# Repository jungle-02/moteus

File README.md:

# moteus brushless servo #

This contains full designs for the moteus brushless servo actuator,
including firmware and PCBs.

**WARNING**: This is not just a software project.  It includes designs
for moderately high power electronics.  It has not yet burned down my
(or anyone's that I know of) house, but there are no guarantees.

# Specifications #

| Name                   | r4.11        | c1         | n1        | x1          |
|------------------------|--------------|------------|-----------|-------------|
| Voltage Input          | 10-44V       | 10-51V     | 10-54V    | 10-54V      |
| Peak Electrical Power  | 900W @ 30V   | 250W @ 28V | 2kW @ 36V | 1.3kW @ 36V |
| Mass                   | 14.2g        | 8.9g       | 14.6g     | 23.8g       |
| Control Rate           | 15-30kHz     | -          | -         | -           |
| PWM Switching Rate     | 15-60kHz     | -          | -         | -           |
| CPU                    | STM32G4      | -          | -         | -           |
| Uncooled phase current | 12A          | 5A         | 9A       | 25A         |
| Cooled phase current   | 32A          | 14A        | 26A       | 62A         |
| Peak phase current     | 100A         | 20A        | 100A      | 120A        |
| Communications         | 5Mbps CAN-FD | -          | -         | -           |
| Dimensions             | 46x53mm      | 38x38x9mm  | 46x46x8mm | 56x56x10mm  |

Assembled and tested boards can be purchased at: https://mjbots.com

# Directory structure #

* hw/ - hardware (mechanical and electrical designs)
  * controller/ - PCB design for moteus-r4.11
  * c1/ - PCB design for moteus-c1
  * n1/ - PCB design for moteus-n1
  * x1/ - PCB design for moteus-x1
* fw/ - firmware for brushless controller
* lib/ - client side software
* utils/ - diagnostic tools
* tools/ - bazel build configure
* docs/ - documentation

# Documentation #

* [Quick Start](https://mjbots.github.io/moteus/quick-start)
* [All Documentation](https://mjbots.github.io/moteus/)
* [Discord](https://discord.gg/W4hUpBb)

# Misc #

 * 

# How to support moteus development #

The easiest way to support development the moteus hardware and firmware is as follows:

1) Buy things from https://mjbots.com
2) Build awesome machines!

That's it!  If for some reason you want to go above and beyond, you can sponsor mjbots through github: https://github.com/sponsors/mjbots

# License #

All files contained in this repository, unless otherwise noted, are
available under an Apache 2.0 License:
https://www.apache.org/licenses/LICENSE-2.0

# Trademark #

mjbots Robotic Systems LLC owns and protects the "mjbots" and "moteus" trademarks in many jurisdictions.

If you want to use these names in your project or product, please read the [Trademark Policy](https://mjbots.com/trademark-policy)

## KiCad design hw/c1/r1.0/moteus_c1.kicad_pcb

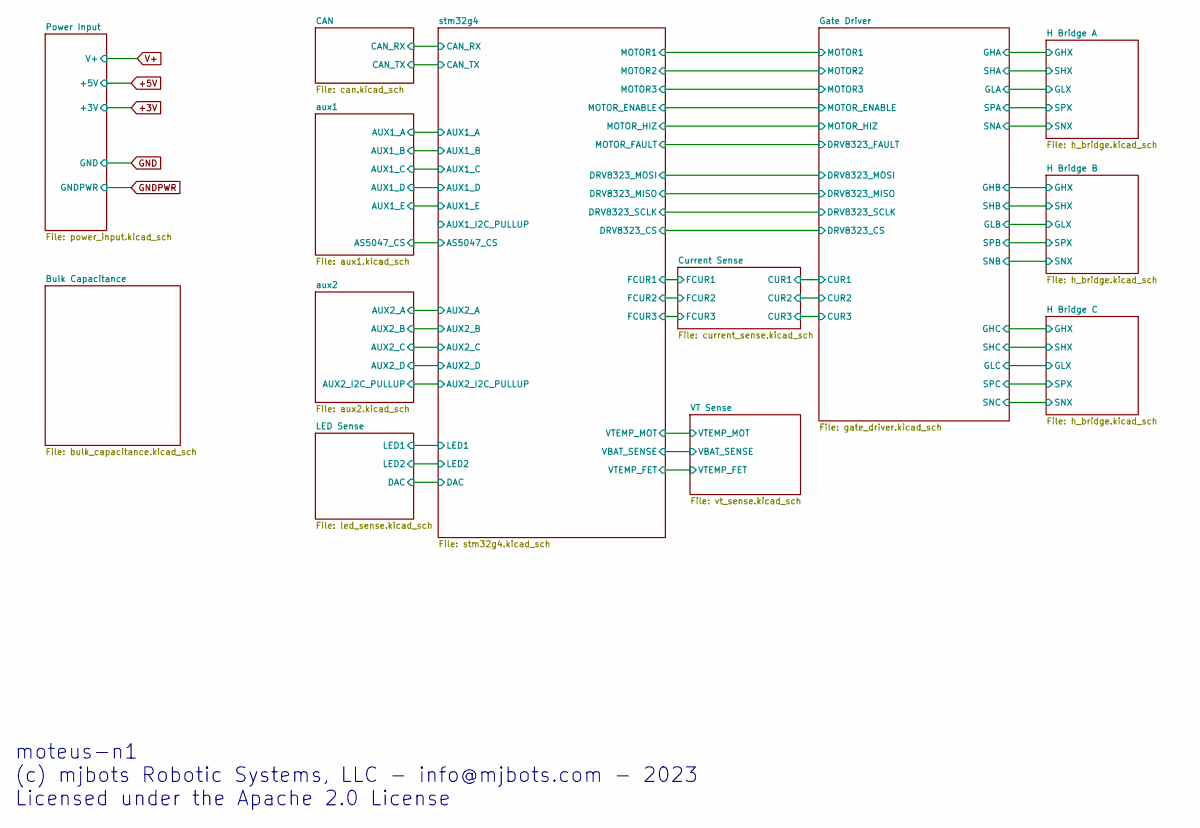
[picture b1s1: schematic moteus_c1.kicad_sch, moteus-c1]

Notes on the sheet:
moteus-n1 (c) mjbots Robotic Systems, LLC - info@mjbots.com - 2023 Licensed under the Apache 2.0 License

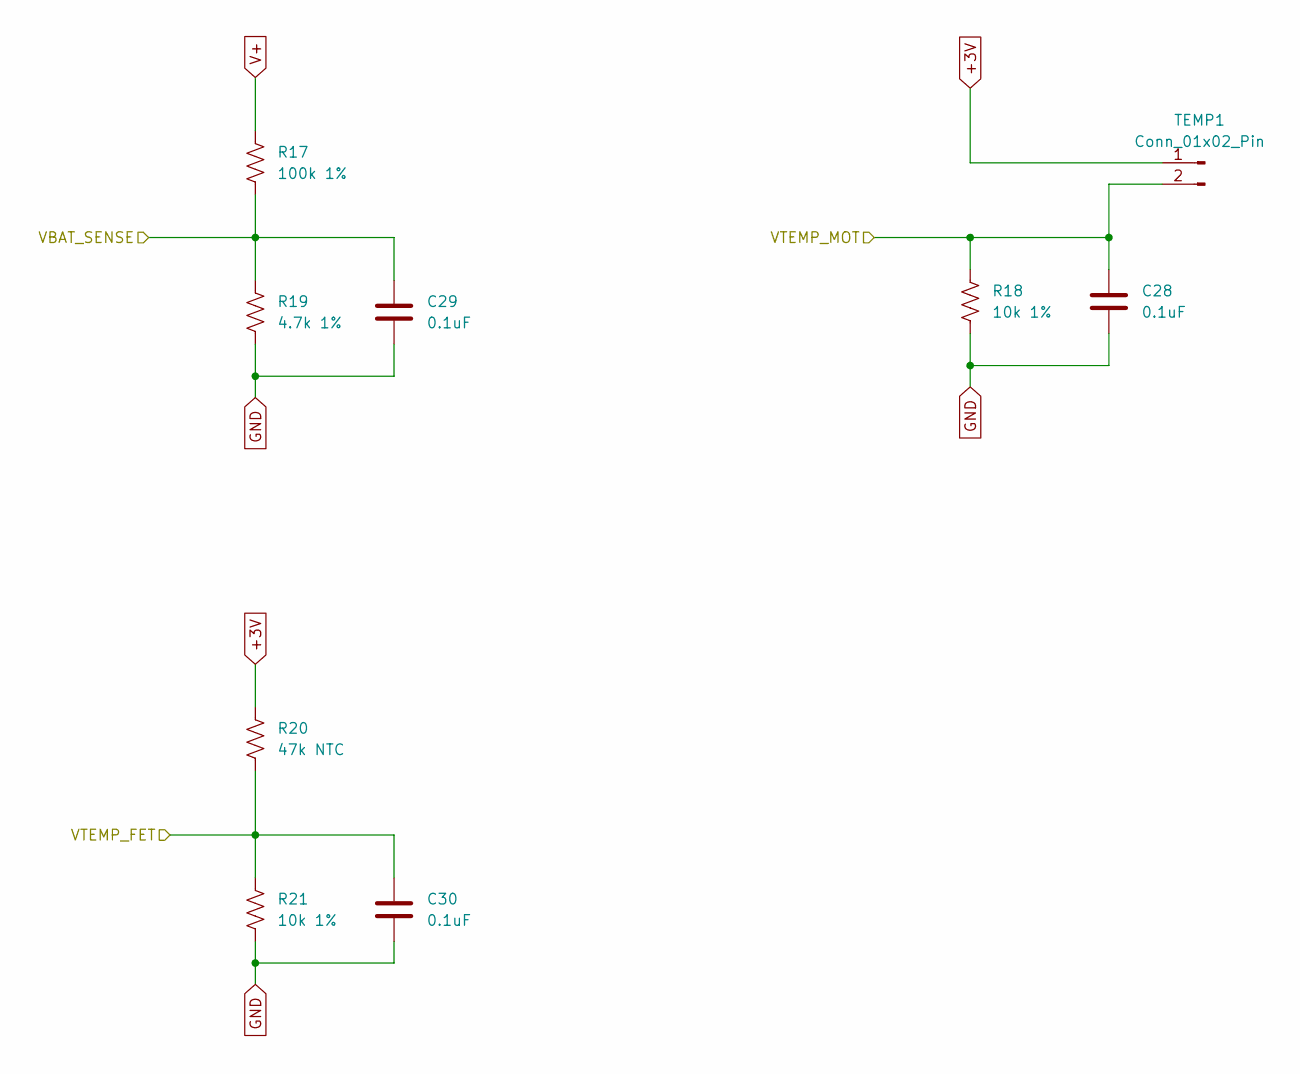
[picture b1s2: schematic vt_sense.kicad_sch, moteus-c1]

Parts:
C28, C29, C30: 0.1uF; C_0402_1005Metric; MPN MF-CAP-0402-0.1uF
R17: 100k 1%; R_0402_1005Metric; MPN RC0402FR-07100KL
R18, R21: 10k 1%; R_0402_1005Metric; MPN RC0402FR-0710KL
R19: 4.7k 1%; R_0402_1005Metric; MPN RC0402FR-074K7L
R20: 47k NTC; R_0402_1005Metric; MPN NCP15WB473F03RC
TEMP1: Conn_01x02_Pin; PinHeader_1x02_P2.00mm_Vertical

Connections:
/VT Sense/VBAT_SENSE: C29.1, R17.2, R19.1; also elsewhere on the board
/VT Sense/VTEMP_FET: C30.1, R20.2, R21.1; also elsewhere on the board
/VT Sense/VTEMP_MOT: C28.1, R18.1, TEMP1.2; also elsewhere on the board
V+: R17.1; also elsewhere on the board

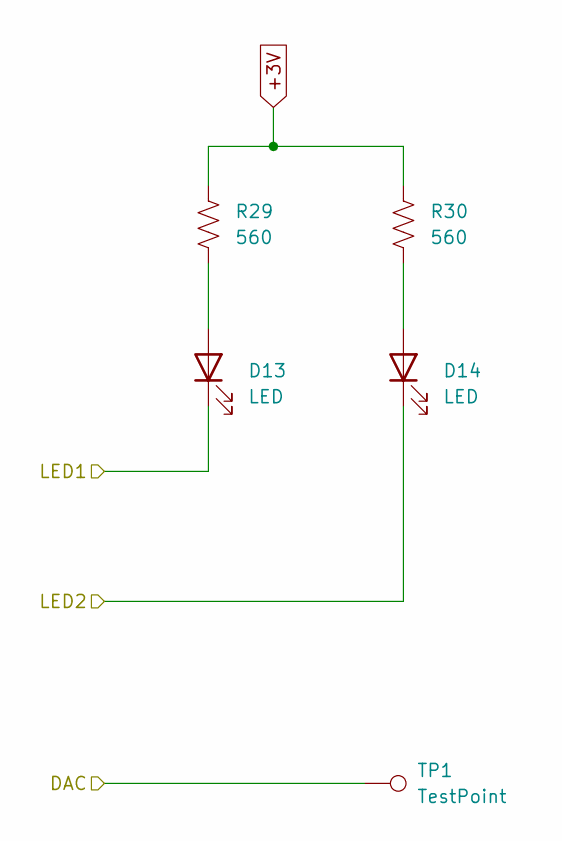
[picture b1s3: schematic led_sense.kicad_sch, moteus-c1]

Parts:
D13: LED; LED_0603_1608Metric; MPN MF-LED-0603-RED
D14: LED; LED_0603_1608Metric; MPN MF-LED-0603-GREEN
R29, R30: 560; R_0402_1005Metric; MPN MF-RES-0402-560
TP1: TestPoint; TestPoint_THTPad_D1.0mm_Drill0.5mm

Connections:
/LED Sense/LED1: D13.1 (K); also elsewhere on the board
/LED Sense/LED2: D14.1 (K); also elsewhere on the board
unnamed: D13.2 (A), R29.2
unnamed: D14.2 (A), R30.2

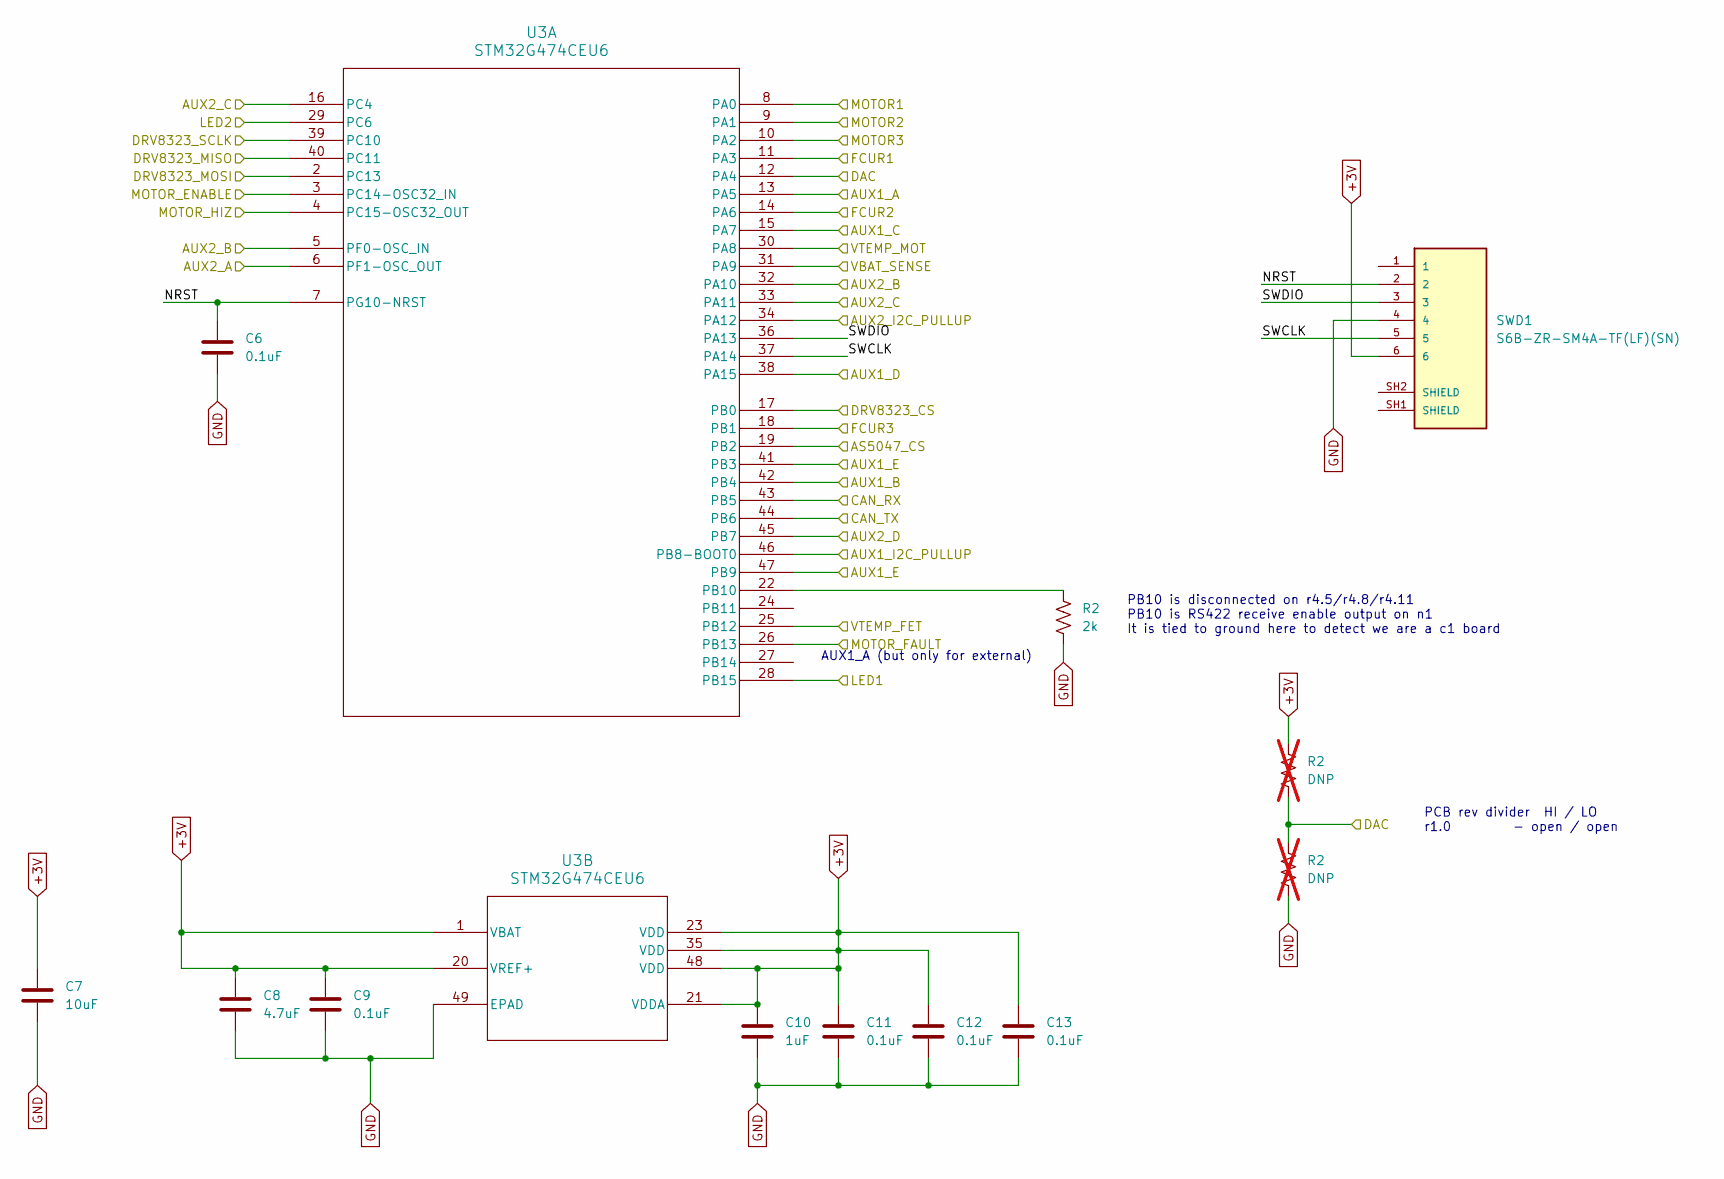
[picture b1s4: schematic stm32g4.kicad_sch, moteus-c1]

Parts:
C6, C9, C11, C12, C13: 0.1uF; C_0402_1005Metric; MPN MF-CAP-0402-0.1uF
C7: 10uF; C_1206_3216Metric; MPN MF-CAP-1206-10uF
C8: 4.7uF; C_0603_1608Metric; MPN CL10A475KP8NNNC
C10: 1uF; C_0402_1005Metric; MPN MF-CAP-0402-1uF
R2: 2k; R_0402_1005Metric; MPN MF-RES-0402-2K
SWD1: S6B-ZR-SM4A-TF(LF)(SN); JST_S6B-ZR-SM4A-TF(LF)(SN); MPN S6B-ZR-SM4A-TF(LF)(SN)
U3: STM32G474CEU6; UFQFPN-48_7X7X0P55MM; MPN STM32G474CEU6

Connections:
/CAN/CAN_RX: U3.43 (PB5); also elsewhere on the board
/CAN/CAN_TX: U3.44 (PB6); also elsewhere on the board
/Current Sense/FCUR1: U3.11 (PA3); also elsewhere on the board
/Current Sense/FCUR2: U3.14 (PA6); also elsewhere on the board
/Current Sense/FCUR3: U3.18 (PB1); also elsewhere on the board
/Gate Driver/DRV8323_CS: U3.17 (PB0); also elsewhere on the board
/Gate Driver/DRV8323_FAULT: U3.26 (PB13); also elsewhere on the board
/Gate Driver/DRV8323_MOSI: U3.2 (PC13); also elsewhere on the board
/Gate Driver/DRV8323_SCLK: U3.39 (PC10); also elsewhere on the board
/Gate Driver/MOTOR1: U3.8 (PA0); also elsewhere on the board
/Gate Driver/MOTOR2: U3.9 (PA1); also elsewhere on the board
/Gate Driver/MOTOR3: U3.10 (PA2); also elsewhere on the board
/Gate Driver/MOTOR_ENABLE: U3.3 (PC14-OSC32_IN); also elsewhere on the board
/Gate Driver/MOTOR_HIZ: U3.4 (PC15-OSC32_OUT); also elsewhere on the board
/LED Sense/LED1: U3.28 (PB15); also elsewhere on the board
/LED Sense/LED2: U3.29 (PC6); also elsewhere on the board
/VT Sense/VBAT_SENSE: U3.31 (PA9); also elsewhere on the board
/VT Sense/VTEMP_FET: U3.25 (PB12); also elsewhere on the board
/VT Sense/VTEMP_MOT: U3.30 (PA8); also elsewhere on the board
/aux1/AS5047_CS: U3.19 (PB2); also elsewhere on the board
/aux1/AUX1_A: U3.13 (PA5); also elsewhere on the board
/aux1/AUX1_B: U3.42 (PB4); also elsewhere on the board
/aux1/AUX1_C: U3.15 (PA7); also elsewhere on the board
/aux1/AUX1_D: U3.38 (PA15); also elsewhere on the board
/aux1/AUX1_E: U3.41 (PB3), U3.47 (PB9); also elsewhere on the board
/aux2/AUX2_A: U3.6 (PF1-OSC_OUT); also elsewhere on the board
/aux2/AUX2_B: U3.5 (PF0-OSC_IN), U3.32 (PA10); also elsewhere on the board
/aux2/AUX2_C: U3.16 (PC4), U3.33 (PA11); also elsewhere on the board
/aux2/AUX2_D: U3.45 (PB7); also elsewhere on the board
/aux2/AUX2_I2C_PULLUP: U3.34 (PA12); also elsewhere on the board
/stm32g4/AUX1_I2C_PULLUP: U3.46 (PB8-BOOT0)
/stm32g4/NRST: C6.1, SWD1.2, U3.7 (PG10-NRST)
/stm32g4/SWCLK: SWD1.5, U3.37 (PA14)
/stm32g4/SWDIO: SWD1.3, U3.36 (PA13)

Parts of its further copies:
R31: 2k; R_0402_1005Metric; MPN MF-RES-0402-2K

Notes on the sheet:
PB10 is disconnected on r4.5/r4.8/r4.11 PB10 is RS422 receive enable output on n1 It is tied to ground here to detect we are a c1 board
PCB rev divider HI / LO r1.0 - open / open
AUX1_A (but only for external)

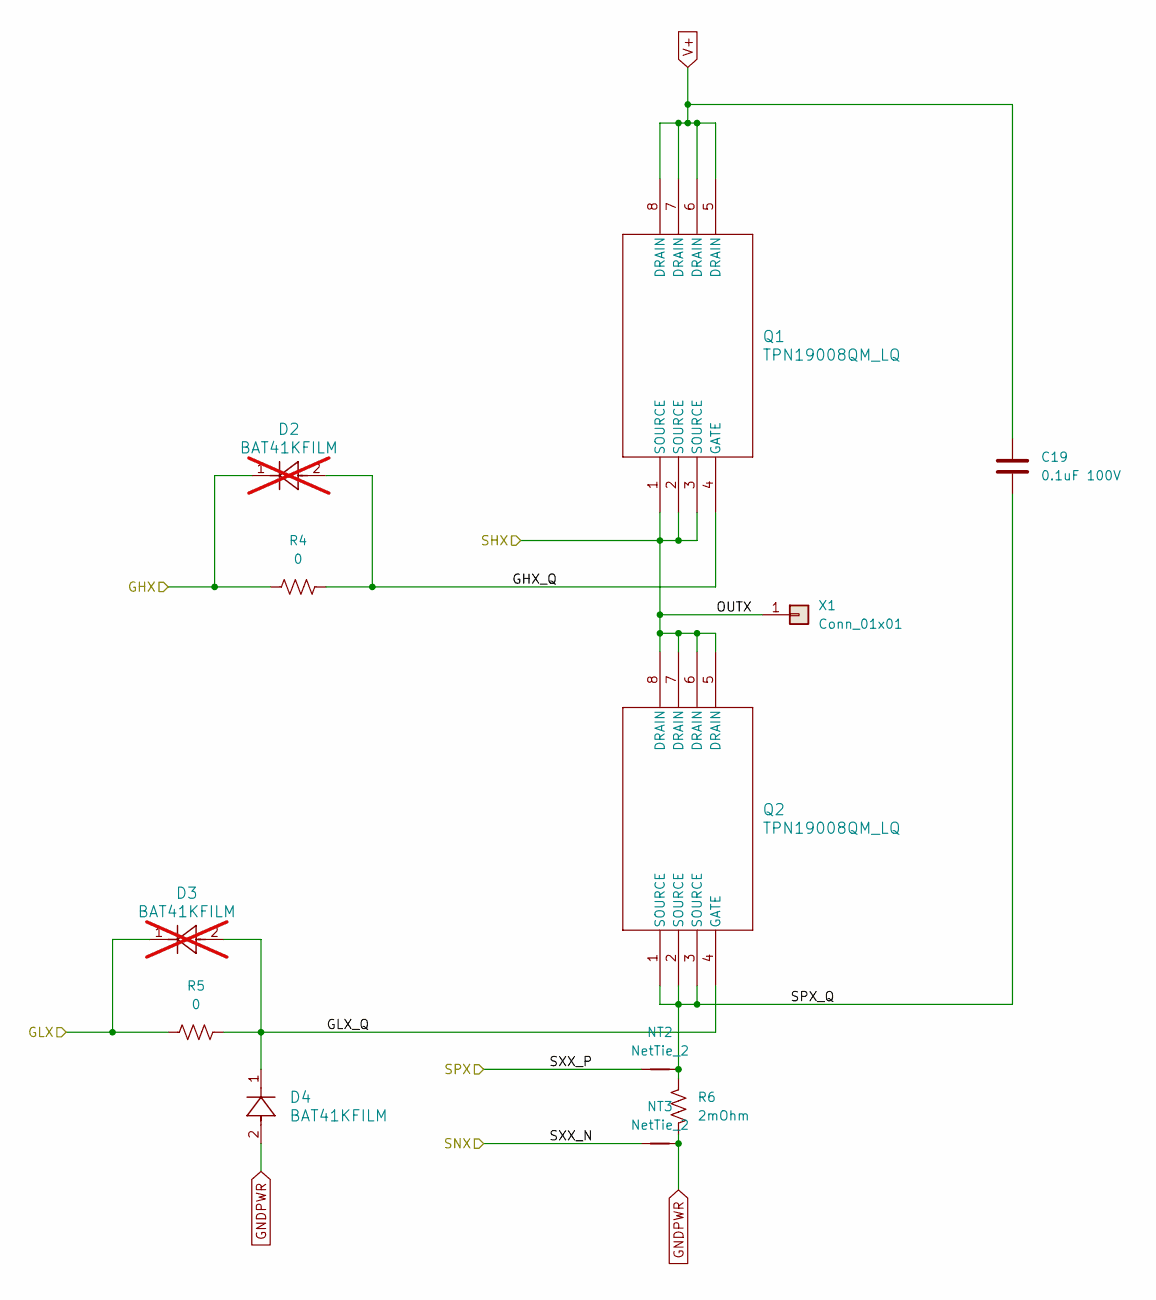
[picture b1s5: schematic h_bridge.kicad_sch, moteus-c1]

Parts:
C19: 0.1uF 100V; C_1206_3216Metric; MPN 12061C104KAT2A
D2, D3: BAT41KFILM; SOD-523_STM; MPN BAT41KFILM; not fitted
D4: BAT41KFILM; SOD-523_STM; MPN BAT41KFILM
NT2, NT3: NetTie_2; NetTie-2_SMD_Pad0.254mm
Q1, Q2: TPN19008QM_LQ; TSON Advance_TOS; MPN TPN19008QM,LQ
R4: 0; R_0402_1005Metric; MPN MF-RES-0402-0
R5: 0; R_0805_2012Metric; MPN MF-RES-0402-0
R6: 2mOhm; R_0805_2012Metric; MPN CSSH0805FT2L00
X1: Conn_01x01; POWER_M2.5

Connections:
/Gate Driver/GHA: D2.1, R4.1; also elsewhere on the board
/Gate Driver/GLA: D3.1, R5.1; also elsewhere on the board
/H Bridge A/GHX_Q: D2.2, Q1.4 (GATE), R4.2
/H Bridge A/GLX_Q: D3.2, D4.1, Q2.4 (GATE), R5.2
/H Bridge A/OUTX: Q1.1 (SOURCE), Q1.2 (SOURCE), Q1.3 (SOURCE), Q2.5 (DRAIN), Q2.6 (DRAIN), Q2.7 (DRAIN), Q2.8 (DRAIN), X1.1; also elsewhere on the board
/H Bridge A/SPX_Q: C19.2, NT2.2, Q2.1 (SOURCE), Q2.2 (SOURCE), Q2.3 (SOURCE), R6.1
/H Bridge A/SXX_N: NT3.1; also elsewhere on the board
/H Bridge A/SXX_P: NT2.1; also elsewhere on the board
GNDPWR: D4.2, NT3.2, R6.2; also elsewhere on the board
V+: C19.1, Q1.5 (DRAIN), Q1.6 (DRAIN), Q1.7 (DRAIN), Q1.8 (DRAIN); also elsewhere on the board

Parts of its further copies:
C20, C21: 0.1uF 100V; C_1206_3216Metric; MPN 12061C104KAT2A
D5, D6, D8, D9: BAT41KFILM; SOD-523_STM; MPN BAT41KFILM; not fitted
D7, D10: BAT41KFILM; SOD-523_STM; MPN BAT41KFILM
NT4, NT5, NT6, NT7: NetTie_2; NetTie-2_SMD_Pad0.254mm
Q3, Q4, Q5, Q6: TPN19008QM_LQ; TSON Advance_TOS; MPN TPN19008QM,LQ
R7, R10: 0; R_0402_1005Metric; MPN MF-RES-0402-0
R8, R11: 0; R_0805_2012Metric; MPN MF-RES-0402-0
R9, R12: 2mOhm; R_0805_2012Metric; MPN CSSH0805FT2L00
X2, X3: Conn_01x01; POWER_M2.5

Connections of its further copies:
/Gate Driver/GHB: D5.1, R7.1; also elsewhere on the board
/Gate Driver/GHC: D8.1, R10.1; also elsewhere on the board
/Gate Driver/GLB: D6.1, R8.1; also elsewhere on the board
/Gate Driver/GLC: D9.1, R11.1; also elsewhere on the board
/H Bridge B/GHX_Q: D5.2, Q3.4 (GATE), R7.2
/H Bridge B/GLX_Q: D6.2, D7.1, Q4.4 (GATE), R8.2
/H Bridge B/OUTX: Q3.1 (SOURCE), Q3.2 (SOURCE), Q3.3 (SOURCE), Q4.5 (DRAIN), Q4.6 (DRAIN), Q4.7 (DRAIN), Q4.8 (DRAIN), X2.1; also elsewhere on the board
/H Bridge B/SPX_Q: C20.2, NT4.2, Q4.1 (SOURCE), Q4.2 (SOURCE), Q4.3 (SOURCE), R9.1
/H Bridge B/SXX_N: NT5.1; also elsewhere on the board
/H Bridge B/SXX_P: NT4.1; also elsewhere on the board
/H Bridge C/GHX_Q: D8.2, Q5.4 (GATE), R10.2
/H Bridge C/GLX_Q: D9.2, D10.1, Q6.4 (GATE), R11.2
/H Bridge C/OUTX: Q5.1 (SOURCE), Q5.2 (SOURCE), Q5.3 (SOURCE), Q6.5 (DRAIN), Q6.6 (DRAIN), Q6.7 (DRAIN), Q6.8 (DRAIN), X3.1; also elsewhere on the board
/H Bridge C/SPX_Q: C21.2, NT6.2, Q6.1 (SOURCE), Q6.2 (SOURCE), Q6.3 (SOURCE), R12.1
/H Bridge C/SXX_N: NT7.1; also elsewhere on the board
/H Bridge C/SXX_P: NT6.1; also elsewhere on the board
GNDPWR: D7.2, D10.2, NT5.2, NT7.2, R9.2, R12.2; also elsewhere on the board
V+: C20.1, C21.1, Q3.5 (DRAIN), Q3.6 (DRAIN), Q3.7 (DRAIN), Q3.8 (DRAIN), Q5.5 (DRAIN), Q5.6 (DRAIN), Q5.7 (DRAIN), Q5.8 (DRAIN); also elsewhere on the board

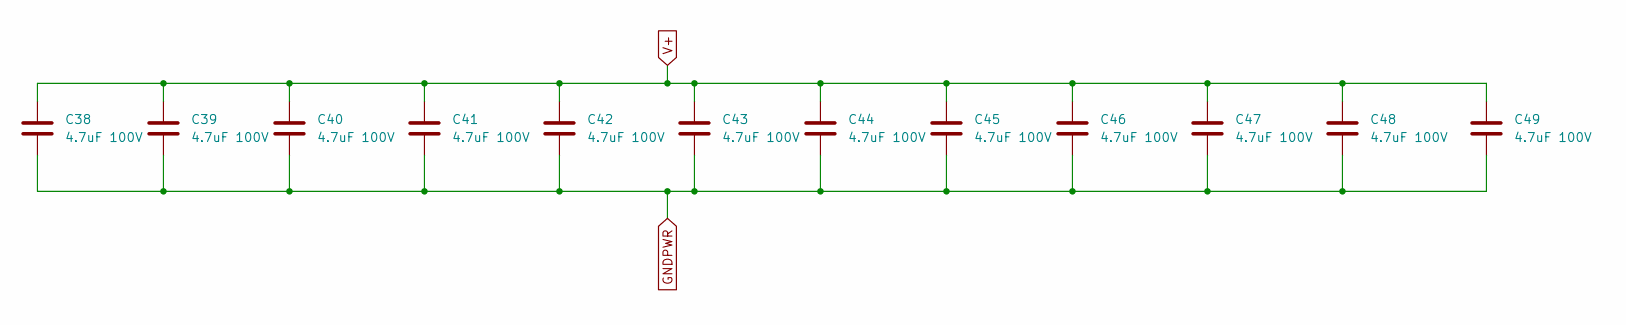
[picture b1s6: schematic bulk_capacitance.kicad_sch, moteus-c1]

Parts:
C38, C39, C40, C41, C42, C43, C44, C45, C46, C47, C48, C49: 4.7uF 100V; C_1206_3216Metric; MPN GRJ31CC72A475KE01K

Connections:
GNDPWR: C38.2, C39.2, C40.2, C41.2, C42.2, C43.2, C44.2, C45.2, C46.2, C47.2, C48.2, C49.2; also elsewhere on the board
V+: C38.1, C39.1, C40.1, C41.1, C42.1, C43.1, C44.1, C45.1, C46.1, C47.1, C48.1, C49.1; also elsewhere on the board

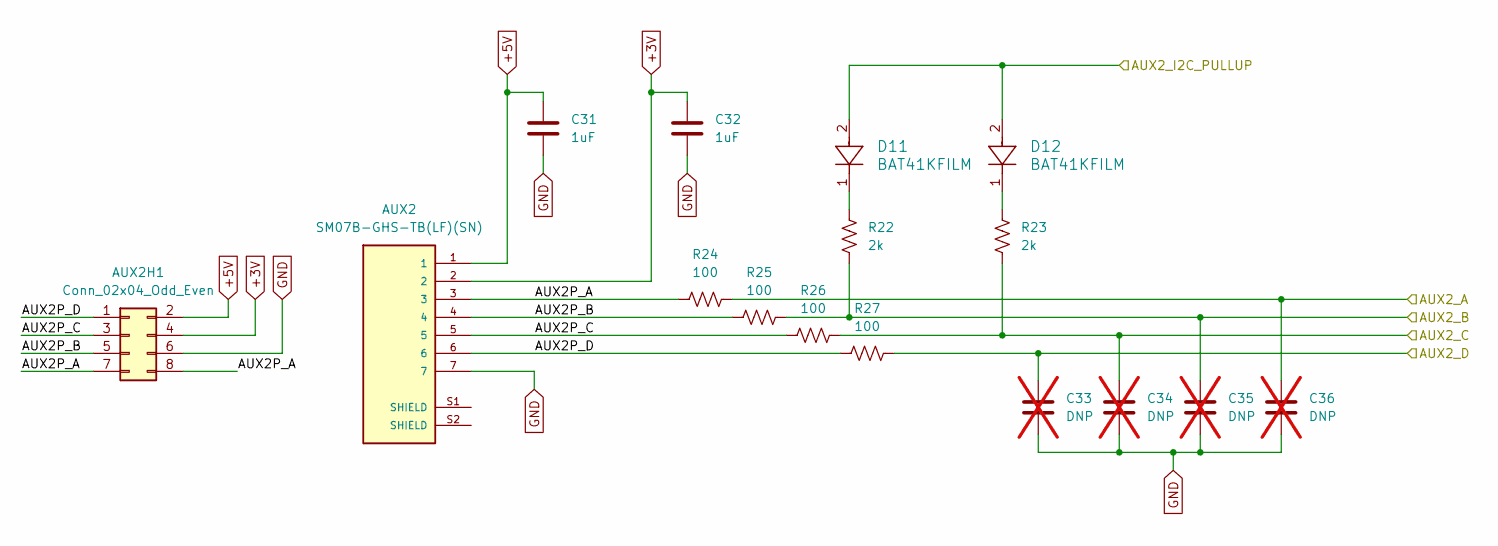
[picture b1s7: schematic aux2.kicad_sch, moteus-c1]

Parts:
AUX2: SM07B-GHS-TB(LF)(SN); JST_SM07B-GHS-TB(LF)(SN); MPN SM07B-GHS-TB(LF)(SN)
AUX2H1: Conn_02x04_Odd_Even; PinHeader_2x04_P1.27mm_Vertical
C31, C32: 1uF; C_0402_1005Metric; MPN MF-CAP-0402-1uF
C33, C34, C35, C36: DNP; C_0402_1005Metric; not fitted
D11, D12: BAT41KFILM; SOD-523_STM; MPN BAT41KFILM
R22, R23: 2k; R_0402_1005Metric; MPN MF-RES-0402-2K
R24, R25, R26, R27: 100; R_0402_1005Metric; MPN MF-RES-0402-100

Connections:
+5V: AUX2.1, AUX2H1.2, C31.1; also elsewhere on the board
/aux2/AUX2P_B: AUX2.4, AUX2H1.5, R25.1
/aux2/AUX2P_C: AUX2.5, AUX2H1.3, R26.1
/aux2/AUX2P_D: AUX2.6, AUX2H1.1, R27.1
/aux2/AUX2_A: C36.1, R24.2; also elsewhere on the board
/aux2/AUX2_B: C35.1, R22.2, R25.2; also elsewhere on the board
/aux2/AUX2_C: C34.1, R23.2, R26.2; also elsewhere on the board
/aux2/AUX2_D: C33.1, R27.2; also elsewhere on the board
/aux2/AUX2_I2C_PULLUP: D11.2, D12.2; also elsewhere on the board
unnamed: D11.1, R22.1
unnamed: D12.1, R23.1

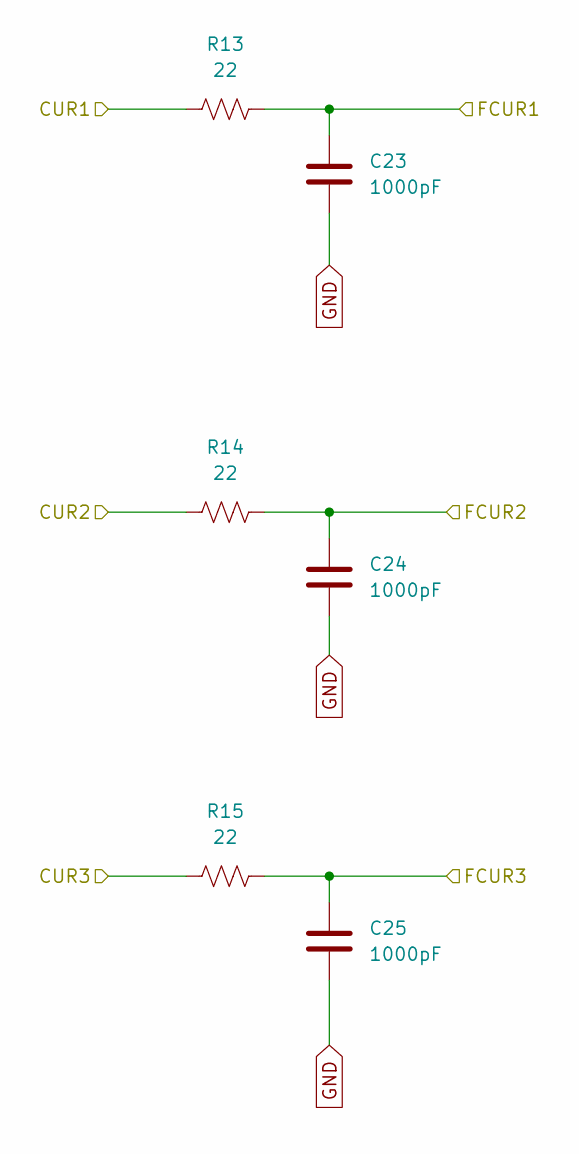
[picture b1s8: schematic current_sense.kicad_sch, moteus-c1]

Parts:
C23, C24, C25: 1000pF; C_0402_1005Metric; MPN MF-CAP-0402-1nF
R13, R14, R15: 22; R_0402_1005Metric; MPN MF-RES-0402-22

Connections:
/Current Sense/CUR1: R13.1; also elsewhere on the board
/Current Sense/CUR2: R14.1; also elsewhere on the board
/Current Sense/CUR3: R15.1; also elsewhere on the board
/Current Sense/FCUR1: C23.1, R13.2; also elsewhere on the board
/Current Sense/FCUR2: C24.1, R14.2; also elsewhere on the board
/Current Sense/FCUR3: C25.1, R15.2; also elsewhere on the board

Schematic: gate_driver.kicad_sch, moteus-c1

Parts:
C14: 1uF 25V; C_0603_1608Metric; MPN C1608X7R1E105K080AE
C15: 0.1uF 100V; C_0603_1608Metric; MPN GCJ188R72A104KA01D
C16: 47nF 100V; C_0603_1608Metric; MPN C0603X473K1RAC7867
C17: 1uF; C_0402_1005Metric; MPN MF-CAP-0402-1uF
C18: 1uF; C_0603_1608Metric; MPN MF-CAP-0603-1uF
R2, R3: 2k; R_0402_1005Metric; MPN MF-RES-0402-2K
U4: DRV8323SRTAR; RTA0040B; MPN DRV8323SRTAR

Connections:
/Current Sense/CUR1: U4.21 (SOC); also elsewhere on the board
/Current Sense/CUR2: U4.22 (SOB); also elsewhere on the board
/Current Sense/CUR3: U4.23 (SOA); also elsewhere on the board
/Gate Driver/DRV8323_CS: U4.29 (GAIN_SCS_N); also elsewhere on the board
/Gate Driver/DRV8323_FAULT: R3.2, U4.25 (FAULT_N); also elsewhere on the board
/Gate Driver/DRV8323_MOSI: U4.27 (IDRIVE_SDI); also elsewhere on the board
/Gate Driver/DRV8323_SCLK: U4.28 (VDS_SCLK); also elsewhere on the board
/Gate Driver/GHA: U4.6 (GHA); also elsewhere on the board
/Gate Driver/GHB: U4.15 (GHB); also elsewhere on the board
/Gate Driver/GHC: U4.16 (GHC); also elsewhere on the board
/Gate Driver/GLA: U4.8 (GLA); also elsewhere on the board
/Gate Driver/GLB: U4.13 (GLB); also elsewhere on the board
/Gate Driver/GLC: U4.18 (GLC); also elsewhere on the board
/Gate Driver/MOTOR1: U4.34 (INHA); also elsewhere on the board
/Gate Driver/MOTOR2: U4.36 (INHB); also elsewhere on the board
/Gate Driver/MOTOR3: U4.38 (INHC); also elsewhere on the board
/Gate Driver/MOTOR_ENABLE: U4.30 (ENABLE); also elsewhere on the board
/Gate Driver/MOTOR_HIZ: U4.35 (INLA), U4.37 (INLB), U4.39 (INLC); also elsewhere on the board
/H Bridge A/OUTX: U4.7 (SHA); also elsewhere on the board
/H Bridge A/SXX_N: U4.10 (SNA); also elsewhere on the board
/H Bridge A/SXX_P: U4.9 (SPA); also elsewhere on the board
/H Bridge B/OUTX: U4.14 (SHB); also elsewhere on the board
/H Bridge B/SXX_N: U4.11 (SNB); also elsewhere on the board
/H Bridge B/SXX_P: U4.12 (SPB); also elsewhere on the board
/H Bridge C/OUTX: U4.17 (SHC); also elsewhere on the board
/H Bridge C/SXX_N: U4.20 (SNC); also elsewhere on the board
/H Bridge C/SXX_P: U4.19 (SPC); also elsewhere on the board
GNDPWR: C15.1, U4.40 (PGND), U4.41 (PAD); also elsewhere on the board
unnamed: C16.2, U4.2 (CPH)
unnamed: C16.1, U4.1 (CPL)
unnamed: C17.2, U4.33 (DVDD)
unnamed: C14.2, U4.3 (VCP)
V+: C14.1, C15.2, U4.4 (VM), U4.5 (VDRAIN); also elsewhere on the board

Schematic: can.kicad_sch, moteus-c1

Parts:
C26, C27: 0.1uF; C_0402_1005Metric; MPN MF-CAP-0402-0.1uF
CAN1: S3B-PH-SM4-TB(LF)(SN); JST_S3B-PH-SM4-TB(LF)(SN); MPN S3B-PH-SM4-TB(LF)(SN)
CAN_DBG1: Conn_01x03_Pin; PinHeader_1x03_P2.00mm_Vertical
R16: 120; R_0805_2012Metric; MPN RC0805FR-07120RL; not fitted
U5: TCAN1057AEV-Q1; SOIC-8_3.9x4.9mm_P1.27mm; MPN TCAN1057AEVDRQ1

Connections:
+5V: C27.1, U5.3 (VCC); also elsewhere on the board
/CAN/CAN_N: CAN1.2, CAN_DBG1.2, R16.2, U5.6 (CANL)
/CAN/CAN_P: CAN1.1, CAN_DBG1.1, R16.1, U5.7 (CANH)
/CAN/CAN_RX: U5.4 (RXD); also elsewhere on the board
/CAN/CAN_TX: U5.1 (TXD); also elsewhere on the board

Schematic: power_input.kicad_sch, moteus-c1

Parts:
C1: 1uF 100V; C_0805_2012Metric; MPN GCM21BC72A105KE36L
C2: 22uF; C_1206_3216Metric; MPN GRM31CR71A226KE15L
C3, C4: 1uF; C_0402_1005Metric; MPN MF-CAP-0402-1uF
C5: 1uF; C_0603_1608Metric; MPN MF-CAP-0603-1uF
D1: SMBJ51D-M3/I; D_SMB; MPN SMBJ51D-M3/I
J1: XT30PW-M; AMASS_XT30PW-M; MPN XT30PW-M
L1: 47uH; IND_4018-WE-LQS_WRE; MPN 74404042470
NT1: NetTie_2; NetTie-2_SMD_Pad0.254mm
R1: 0; R_0402_1005Metric; MPN MF-RES-0402-0
U1: MAX15062BATA+T; 21-0487A_MXM; MPN MAX15062BATA+T
U2: TLV70233DSER; DSE0006A; MPN TLV70233DSER
VN1: Conn_01x01; POWER_M2.5
VP1: Conn_01x01; POWER_M2.5

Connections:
+5V: C2.1, C3.1, L1.1, U1.4 (FB/VOUT), U2.1 (IN); also elsewhere on the board
GNDPWR: C1.2, C5.2, D1.2 (A2), J1.N, NT1.1, VN1.1; also elsewhere on the board
unnamed: L1.2, U1.8 (LX)
unnamed: R1.1, U1.5 (MODE)
unnamed: C5.1, U1.3 (VCC)
V+: C1.1, D1.1 (A1), J1.P, U1.1 (VIN), U1.2 (EN/UVLO), VP1.1; also elsewhere on the board

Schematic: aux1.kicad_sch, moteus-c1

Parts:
AUX1: Conn_01x04; PinHeader_1x04_P1.27mm_Vertical
C37: 0.1uF; C_0402_1005Metric; MPN MF-CAP-0402-0.1uF
R24: 100; R_0402_1005Metric; MPN MF-RES-0402-100
R28: 0; R_0402_1005Metric; MPN MF-RES-0402-0
U6: AS5047P-ATSM; TSSOP14_OSM; MPN AS5047P-ATSM

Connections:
/aux1/AS5047_CS: U6.1 (CSn); also elsewhere on the board
/aux1/AUX1_A: U6.2 (CLK); also elsewhere on the board
/aux1/AUX1_B: U6.3 (MISO); also elsewhere on the board
/aux1/AUX1_C: U6.4 (MOSI); also elsewhere on the board
/aux2/AUX2_A: R24.2; also elsewhere on the board
unnamed: R28.1, U6.11 (VDD)

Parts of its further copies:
R34, R35: 100; R_0402_1005Metric; MPN MF-RES-0402-100

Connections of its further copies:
/aux1/AUX1_D: R34.2; also elsewhere on the board
/aux1/AUX1_E: R35.2; also elsewhere on the board

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
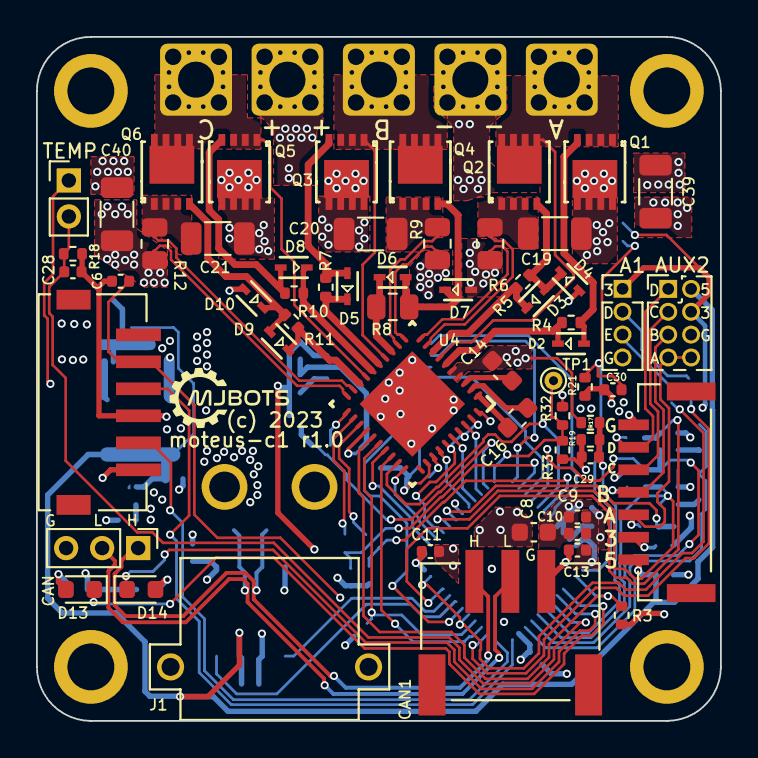
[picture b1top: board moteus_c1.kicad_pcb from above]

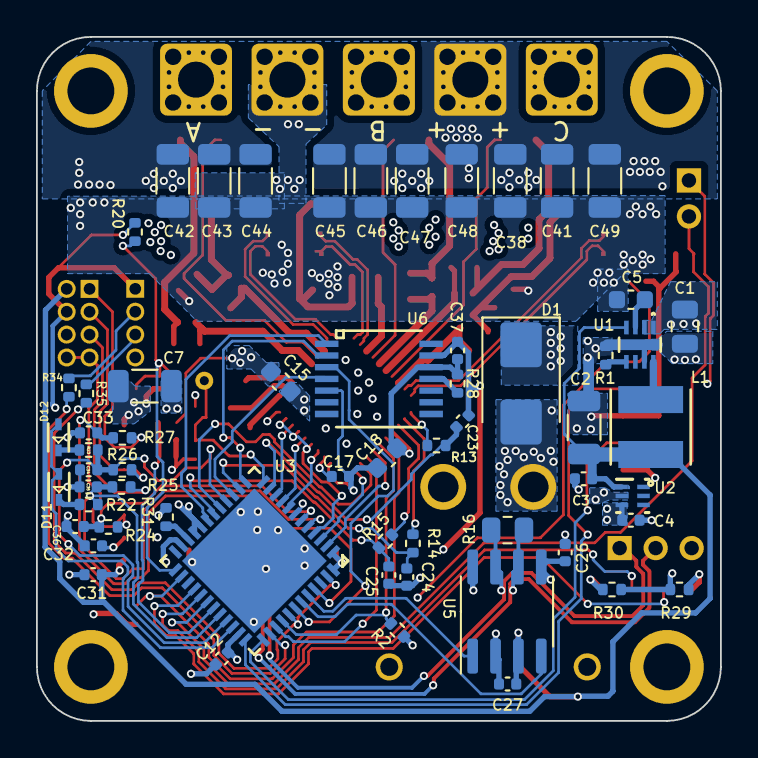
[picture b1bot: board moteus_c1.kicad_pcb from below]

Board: 4 copper layers, 38.0 x 38.0 mm, 135 parts (61 on the bottom side), 88 nets.

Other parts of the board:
MOUNT1, MOUNT2, MOUNT3, MOUNT4: M2.5_MOUNT
R32, R33: DNP; R_0402_1005Metric

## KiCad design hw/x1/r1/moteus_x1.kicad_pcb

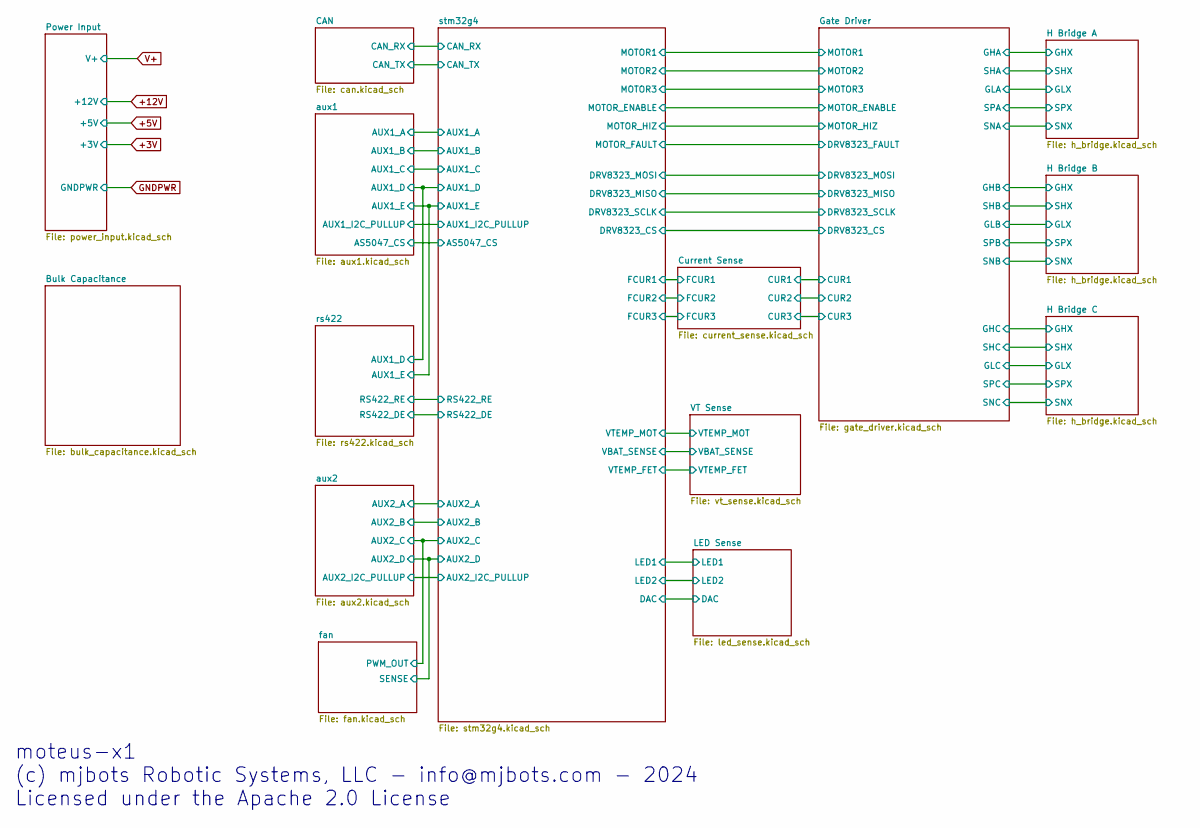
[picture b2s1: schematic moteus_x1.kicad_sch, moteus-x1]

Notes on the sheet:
moteus-x1 (c) mjbots Robotic Systems, LLC - info@mjbots.com - 2024 Licensed under the Apache 2.0 License

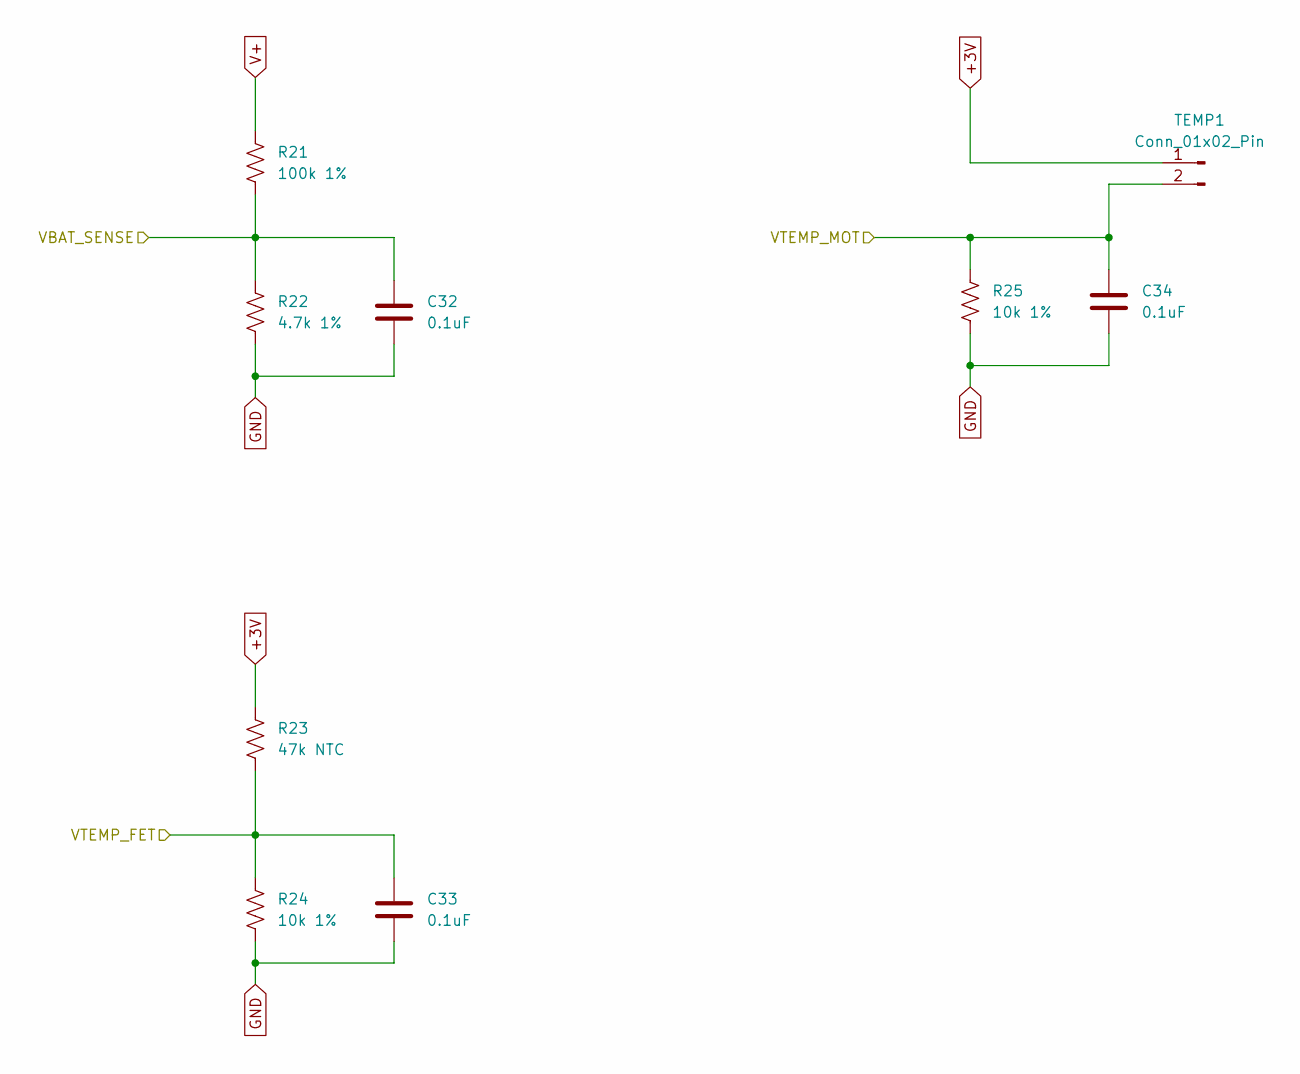
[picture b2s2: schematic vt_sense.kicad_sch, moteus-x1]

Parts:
C32, C33, C34: 0.1uF; C_0402_1005Metric; MPN MF-CAP-0402-0.1uF
R21: 100k 1%; R_0402_1005Metric; MPN RC0402FR-07100KL
R22: 4.7k 1%; R_0402_1005Metric; MPN RC0402FR-074K7L
R23: 47k NTC; R_0402_1005Metric; MPN NCP15WB473F03RC
R24, R25: 10k 1%; R_0402_1005Metric; MPN RC0402FR-0710KL
TEMP1: Conn_01x02_Pin; PinHeader_1x02_P2.54mm_Vertical

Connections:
+3V: R23.1, TEMP1.1; also elsewhere on the board
/VT Sense/VBAT_SENSE: C32.1, R21.2, R22.1; also elsewhere on the board
/VT Sense/VTEMP_FET: C33.1, R23.2, R24.1; also elsewhere on the board
/VT Sense/VTEMP_MOT: C34.1, R25.1, TEMP1.2; also elsewhere on the board
GND: C32.2, C33.2, C34.2, R22.2, R24.2, R25.2; also elsewhere on the board
V+: R21.1; also elsewhere on the board

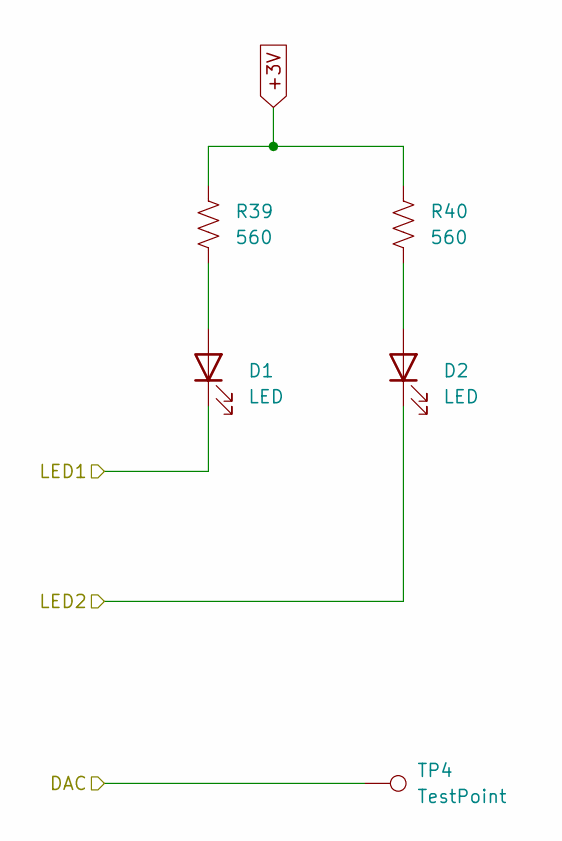
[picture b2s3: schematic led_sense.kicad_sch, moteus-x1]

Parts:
D1: LED; LED_0603_1608Metric; MPN MF-LED-0603-RED
D2: LED; LED_0603_1608Metric; MPN MF-LED-0603-GREEN
R39, R40: 560; R_0402_1005Metric; MPN MF-RES-0402-560
TP4: TestPoint; TestPoint_THTPad_D1.0mm_Drill0.5mm

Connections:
+3V: R39.1, R40.1; also elsewhere on the board
/LED Sense/DAC: TP4.1; also elsewhere on the board
/LED Sense/LED1: D1.1 (K); also elsewhere on the board
/LED Sense/LED2: D2.1 (K); also elsewhere on the board
unnamed: D1.2 (A), R39.2
unnamed: D2.2 (A), R40.2

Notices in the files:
hw/c1/r1.0/moteus_c1.kicad_pcb:
(c) 2023
hw/x1/r1/moteus_x1.kicad_pcb:
(c) 2024
